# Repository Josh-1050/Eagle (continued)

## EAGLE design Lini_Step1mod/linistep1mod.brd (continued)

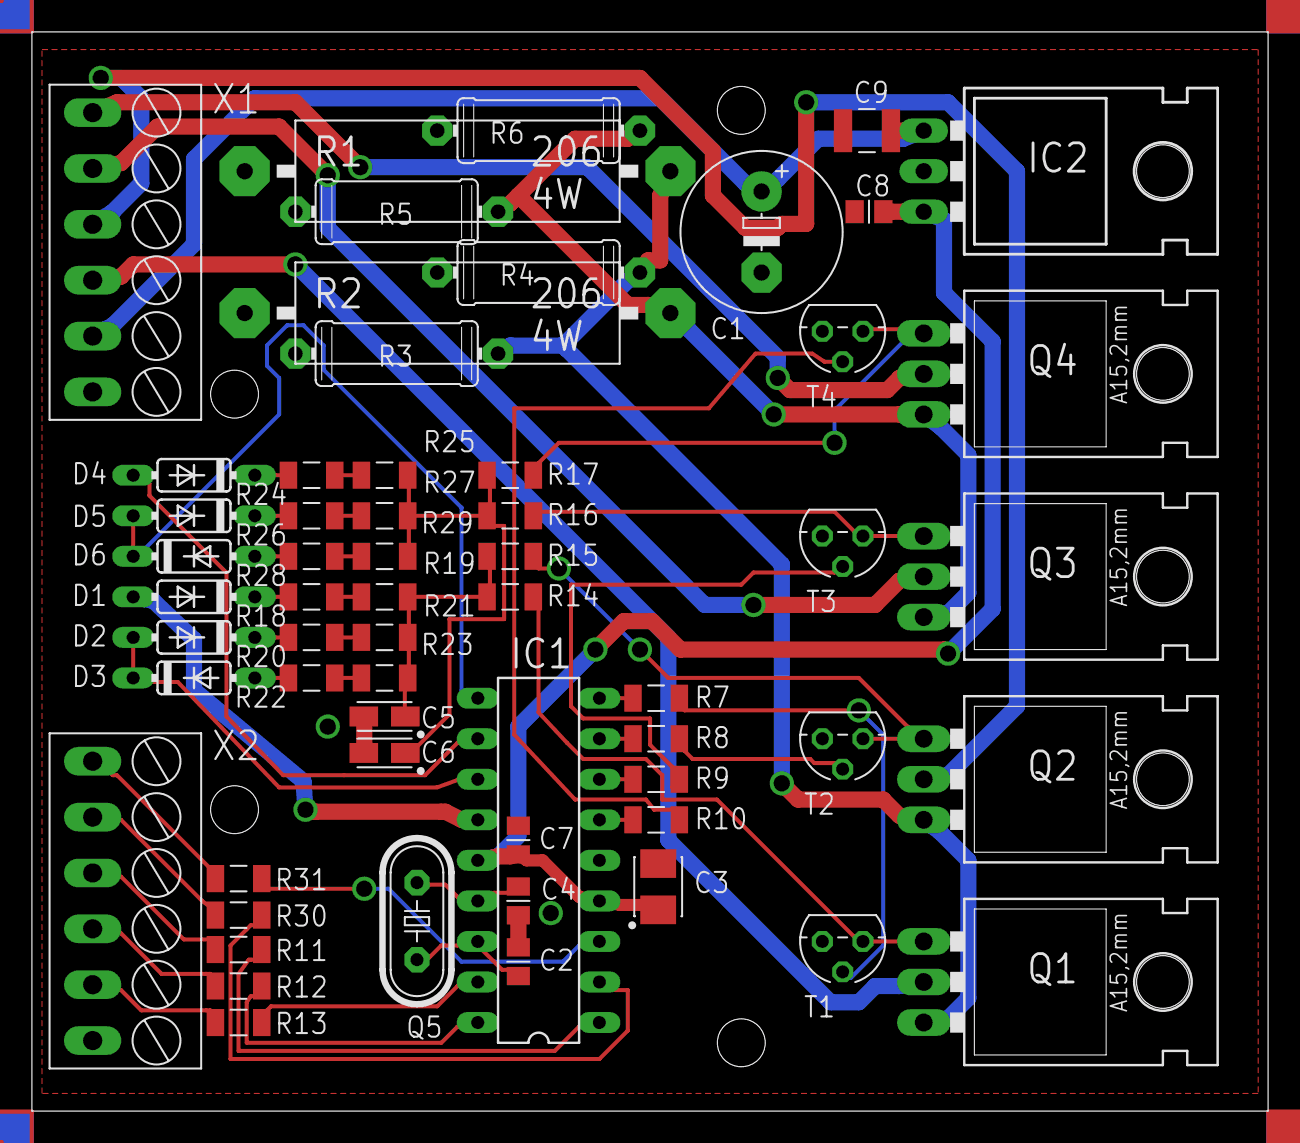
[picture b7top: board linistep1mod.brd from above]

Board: 2 copper layers, 77.5 x 67.6 mm, 63 parts (0 on the bottom side), 51 nets.

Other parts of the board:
U$2, U$3, U$4, U$5: PASSMARK

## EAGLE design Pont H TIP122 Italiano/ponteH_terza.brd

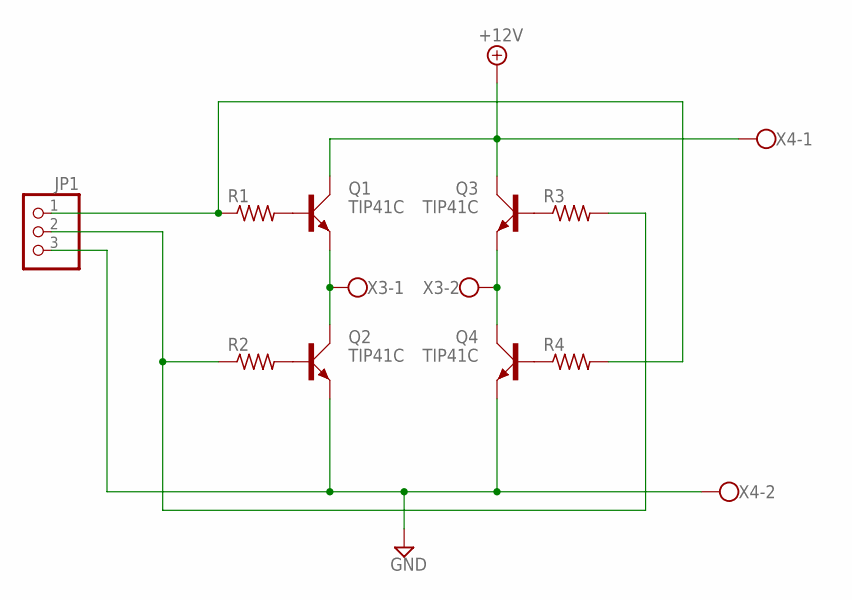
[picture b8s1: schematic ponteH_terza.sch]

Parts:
JP1: PINHD-1X3; 1X03
Q1, Q2, Q3, Q4: TIP41C; TO220AV
R1, R2, R3, R4: R-US_0207/10; 0207/10
X3, X4: W237-02P; W237-132

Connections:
+12V: Q1.C, Q3.C, X4.1
GND: JP1.3, Q2.E, Q4.E, X4.2
unnamed: Q1.B, R1.2
unnamed: Q2.B, R2.2
unnamed: Q3.B, R3.1
unnamed: Q4.B, R4.1
unnamed: JP1.1, R1.1, R4.2
unnamed: JP1.2, R2.1, R3.2
unnamed: Q3.E, Q4.C, X3.2
unnamed: Q1.E, Q2.C, X3.1

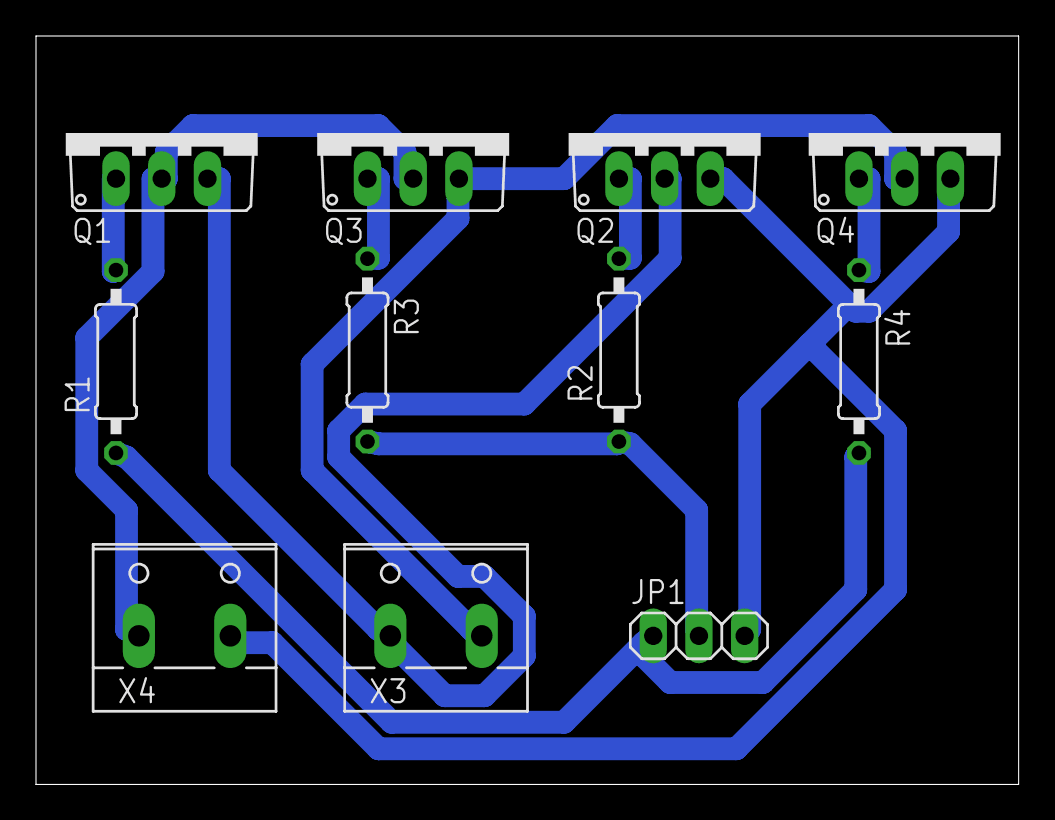
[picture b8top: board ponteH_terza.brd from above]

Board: 2 copper layers, 54.6 x 41.6 mm, 11 parts (0 on the bottom side), 10 nets.

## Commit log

2015-07-06 Projetos Eagle
2015-12-16 Arduino-GRBL connect to CNC3AX
2015-12-18 acertos na pcb
2016-09-10 Gerador
2016-09-10 atualizado
2016-09-16 Projetos
